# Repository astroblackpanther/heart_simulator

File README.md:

# Heart Simulator Project

## Project Overview
A comprehensive heart simulator project developed during the **International Summer Program Exchange** between **ULACIT (Costa Rica)** and **Rice University (USA)**. This project was completed at the **Oshman Engineering Design Kitchen (OEDK)** as part of the **Rice University George R. Brown School of Engineering and Computing**.

## International Collaboration
- **Home Institution**: ULACIT (Universidad Latinoamericana de Ciencia y Tecnología)
- **Host Institution**: Rice University
- **Program**: International Summer Program Exchange
- **Location**: OEDK (Oshman Engineering Design Kitchen), Rice University
- **Academic Unit**: George R. Brown School of Engineering and Computing

## Project Description
This heart simulator project integrates multiple engineering disciplines including:
- **Biomedical Engineering**: Heart physiology simulation
- **Electrical Engineering**: Circuit design and PCB development
- **Mechanical Engineering**: 3D printed components and mechanical systems
- **Computer Engineering**: Arduino programming and control systems

## Project Structure

### 3D Printing Files
Contains STL files for 3D printed components of the heart simulator, including the main heart model and supporting structures.

### Arduino Code
- **3PIN LCD/ULACIT_2025_3PIN**: Arduino code for 3-pin LCD display configuration
- **4PIN LCD - I2C/ULACIT_2025_4PIN_I2C**: Arduino code for 4-pin I2C LCD display configuration

### KiCad Files
- **Main Schematic ULACIT 2025**: Complete KiCad project files including:
  - `.kicad_prl`: Project file
  - `.kicad_sch`: Schematic design
  - `.kicad_pro`: Project configuration
  - `.kicad_pcb`: PCB layout
  - `.step`: 3D model files
  - `.net`: Netlist files

### PCB Production Board Files
- **GERBER-ULACIT 2025 Button Board**: Manufacturing files for the button control board
- **GERBER-ULACIT 2025 Main Board**: Manufacturing files for the main control board
- Includes `.gbr` (GERBER), `.drl` (drill), and `.pdf` files for PCB production

## Academic Collaboration
This project was developed as part of an international exchange program between ULACIT (Universidad Latinoamericana de Ciencia y Tecnología) and Rice University's George R. Brown School of Engineering and Computing, completed at the Oshman Engineering Design Kitchen (OEDK).

## Future Exploration and Development
Since each participant worked individually on this project, we each possess our own complete set of components including the custom PCBs, 3D printed designs, and fully functional heart simulator. This individual ownership opens up exciting possibilities for continued development and exploration.

### Real-Time Heart Beat Integration
One of the most exciting and viable areas that I am interested in exploring in future development is connecting the LED heart simulation to actual real-time heart beats. I believe that this would create a direct visual representation of your actual heart rhythm, allowing you to see the difference between simulated and real heart beats through the LED patterns. This integration could be achieved through several practical approaches:

#### Wearable Device Integration
- **Smartwatch/Activity Tracker**: Connect to devices like Apple Watch, Fitbit, or Garmin through Bluetooth Low Energy (BLE) to read real-time heart rate data and sync it directly to the LED heart
- **Chest Strap Monitors**: Interface with professional heart rate monitors used in sports and medical applications for high-accuracy heart rate data
- **Smartphone Apps**: Utilize phone-based heart rate monitoring through camera and flash technology, making it accessible to anyone with a smartphone

#### Advanced Features and Applications
- **Real-Time Visualization**: LED patterns that directly mirror actual heart rhythm variations, creating a living, breathing heart display
- **Arrhythmia Detection**: Visual alerts when irregular heartbeats are detected, providing immediate feedback on cardiac health
- **Stress Response Monitoring**: Track how heart rate changes during different activities, exercise, or stress levels
- **Data Logging and Analysis**: Record and analyze heart rate patterns over time for health tracking and research purposes
- **Educational Demonstrations**: Show real-time differences between healthy and stressed heart rhythms for medical education

#### AI/ML Integration and Technical Implementation
- **Machine Learning Algorithms**: Develop predictive models to forecast heart rate patterns and optimize LED animations based on individual physiology
- **Pattern Recognition**: Use AI to identify normal vs. abnormal heart rhythms, stress patterns, and health trends
- **Personalized Health Insights**: Implement AI-driven analysis to provide personalized health recommendations and early warning systems
- **Wireless Communication**: Implement WiFi or Bluetooth modules for seamless data transmission from wearable devices
- **Health Platform Integration**: Connect to health platforms like Apple HealthKit, Google Fit, or Fitbit API for comprehensive health data
- **Cloud Connectivity**: Store and analyze heart rate data for long-term health monitoring and research applications
- **Real-Time Processing**: Optimize the system for immediate response to heart rate changes with minimal latency

### Additional Enhancement Areas
- **AI-Powered Mobile Apps**: Create intelligent companion applications with real-time health analysis and personalized recommendations
- **Machine Learning Research Platform**: Develop the system as a research tool for cardiovascular AI/ML studies and algorithm development
- **Educational Software**: Develop interactive learning modules for medical students with AI-driven case studies and pattern recognition training
- **Research Applications**: Adapt for use in cardiovascular research studies, including AI-based health outcome prediction
- **Commercial Potential**: Explore opportunities for educational or medical device markets with AI-enhanced diagnostic capabilities

### Space Applications and Research
The heart simulator's compact design, low power consumption, and robust construction make it an excellent candidate for space-based applications and research:

#### **Astronaut Health Monitoring**
- **Long-Duration Missions**: Monitor cardiovascular health during extended space travel (Mars missions, lunar bases)
- **Microgravity Effects**: Study how space conditions affect heart rate patterns and cardiovascular adaptation
- **Stress Response**: Track physiological responses to space environment stressors and mission events
- **Preventive Medicine**: Early detection of cardiovascular changes that could affect mission safety

#### **Deep Space Exploration**
- **Mars Mission Readiness**: Test cardiovascular monitoring systems for future Mars missions
- **Autonomous Operation**: Develop self-contained monitoring systems for missions with limited ground support
- **Radiation Effects**: Study how cosmic radiation affects cardiovascular function over extended periods
- **Isolation Studies**: Monitor heart health during long periods of isolation and confinement

#### **Space Research and Development**
- **AI-Enhanced Biomedical Experiments**: Conduct controlled studies on cardiovascular adaptation to space conditions using machine learning for pattern analysis
- **Intelligent Health Monitoring**: Implement AI-driven health prediction systems for long-duration space missions
- **Technology Validation**: Test new AI/ML monitoring technologies in the challenging space environment
- **International Collaboration**: Partner with space agencies worldwide for collaborative AI/ML research in space medicine
- **Educational Outreach**: Inspire future generations through space-based biomedical research with AI integration

This project serves as an excellent foundation for continued innovation in biomedical engineering, combining hardware design, software development, and real-world medical applications.

## Acknowledgments
- **ULACIT**: For the international exchange opportunity
- **Rice University**: For hosting and providing world-class facilities and the knowledge.
- **OEDK Staff**: For guidance and support during the project
---

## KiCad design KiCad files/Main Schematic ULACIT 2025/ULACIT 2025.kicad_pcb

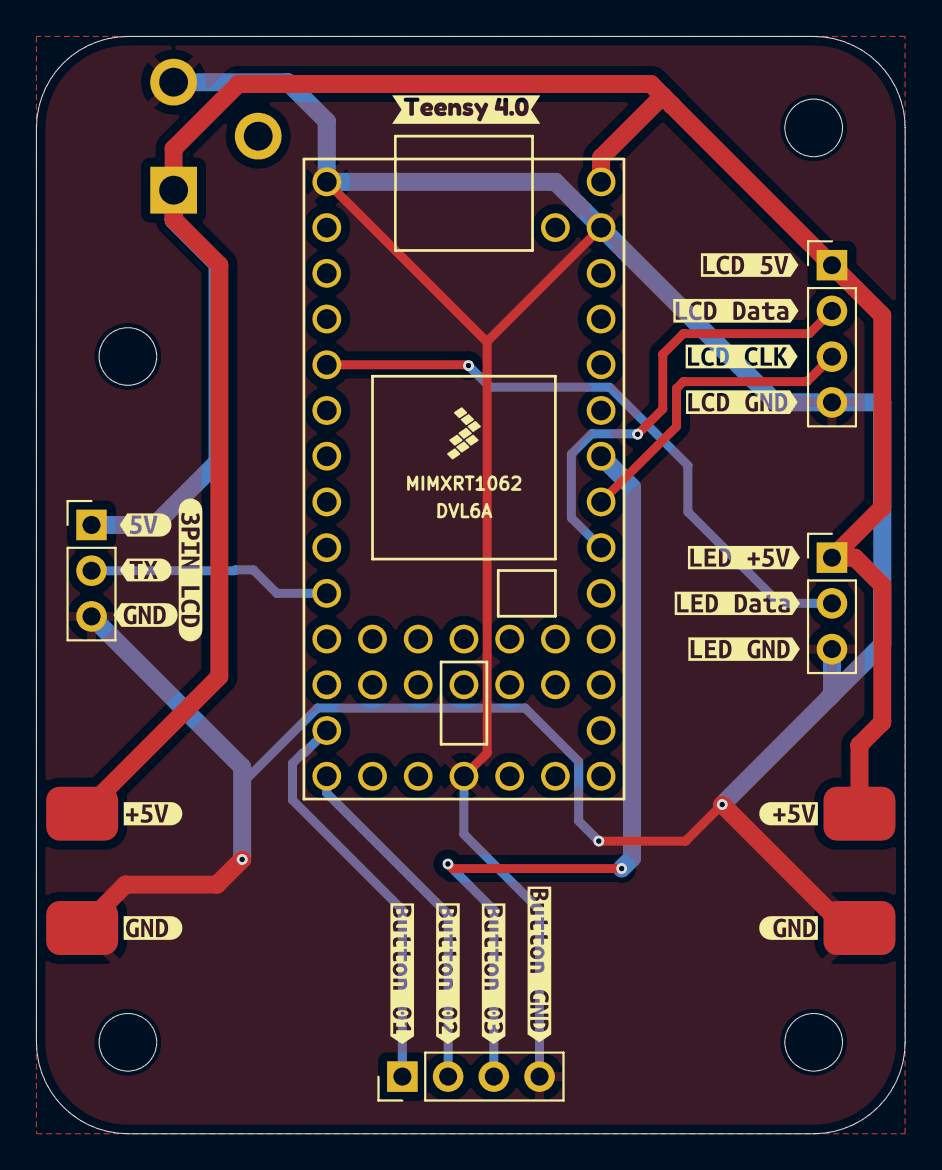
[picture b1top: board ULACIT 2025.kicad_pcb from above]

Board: 2 copper layers, 48.3 x 61.0 mm, 26 parts (1 on the bottom side), 9 nets.

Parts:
J1: Barrel_Jack; BarrelJack_CUI_PJ-102AH_Horizontal
J2: Button Terminal; PinHeader_1x04_P2.54mm_Vertical
J3: LCD Terminal; PinHeader_1x04_P2.54mm_Vertical
J4: LED Terminal; PinHeader_1x03_P2.54mm_Vertical
J6: [OLD] LCD Terminal; PinHeader_1x03_P2.54mm_Vertical
U1: Teensy4.0; Teensy
kibuzzard-6846F3E4: G***; kibuzzard-6846F3E4
kibuzzard-6846F3F3: G***; kibuzzard-6846F3F3
kibuzzard-6846F40C: G***; kibuzzard-6846F40C
kibuzzard-6846F41F: G***; kibuzzard-6846F41F
kibuzzard-68389B9F: G***; kibuzzard-68389B9F
kibuzzard-68389B69: G***; kibuzzard-68389B69
kibuzzard-68389B78: G***; kibuzzard-68389B78
kibuzzard-68389B91: G***; kibuzzard-68389B91
kibuzzard-682631CB: G***; kibuzzard-682631CB
kibuzzard-682631E3: G***; kibuzzard-682631E3
kibuzzard-682631F2: G***; kibuzzard-682631F2
kibuzzard-682633A0: G***; kibuzzard-682633A0
kibuzzard-6826302B: G***; kibuzzard-6826302B
kibuzzard-6826303F: G***; kibuzzard-6826303F
kibuzzard-6838990E: G***; kibuzzard-6838990E
kibuzzard-68263181: G***; kibuzzard-68263181
kibuzzard-68263383: G***; kibuzzard-68263383
kibuzzard-68263394: G***; kibuzzard-68263394
kibuzzard-68263405: G***; kibuzzard-68263405
kibuzzard-68389467: G***; kibuzzard-68389467

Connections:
+5V: J1.1, J3.1, J4.1, J6.1, U1.33 (VIN)
GND: J1.2, J2.4, J3.4, J4.3, J6.3, U1.1 (GND), U1.17 (GND), U1.32 (GND)
unnamed: J2.1, U1.13 (11_MOSI_CTX1)
unnamed: J2.2, U1.14 (12_MISO_MQSL)
unnamed: J2.3, U1.27 (20_A6_TX5_LRCLK1)
unnamed: J3.2, U1.25 (18_A4_SDA0)
unnamed: J3.3, U1.26 (19_A5_SCL0)
unnamed: J4.2, U1.5 (3_LRCLK2)
unnamed: J6.2, U1.10 (8_TX2_IN1)

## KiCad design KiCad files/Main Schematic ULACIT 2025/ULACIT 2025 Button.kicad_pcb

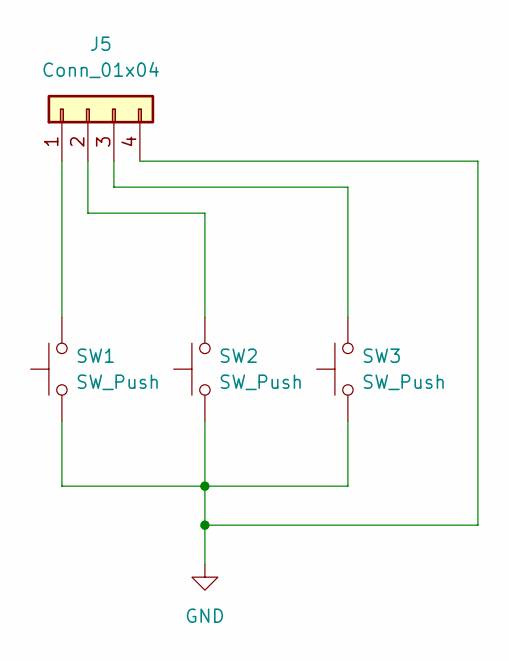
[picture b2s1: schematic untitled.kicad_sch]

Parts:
J5: Conn_01x04; PinHeader_1x04_P2.54mm_Vertical
SW1, SW2, SW3: SW_Push; SW_PUSH_6mm

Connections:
GND: J5.4, SW1.1, SW2.1, SW3.1
unnamed: J5.1, SW1.2
unnamed: J5.2, SW2.2
unnamed: J5.3, SW3.2

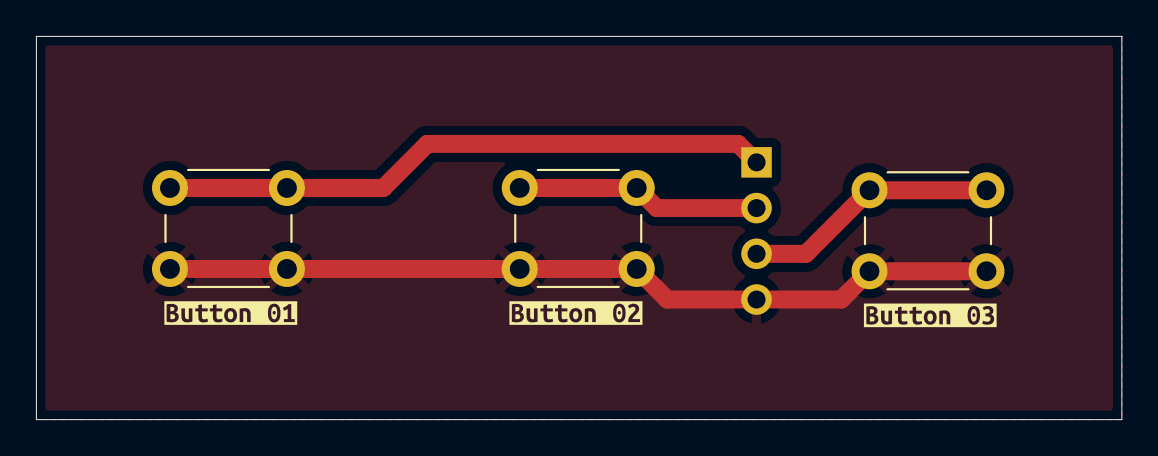
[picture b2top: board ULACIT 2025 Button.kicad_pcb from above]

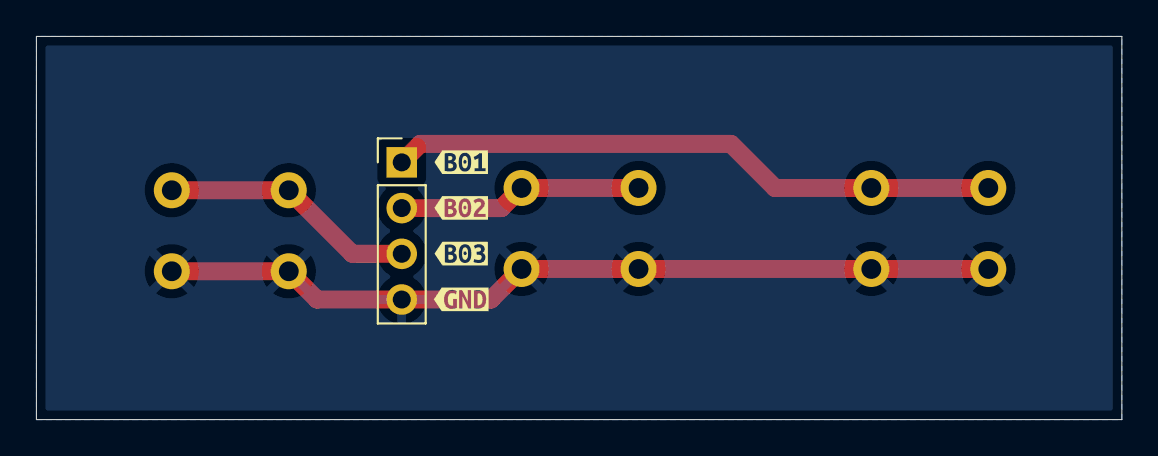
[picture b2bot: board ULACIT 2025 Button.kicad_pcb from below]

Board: 2 copper layers, 60.3 x 21.3 mm, 11 parts (5 on the bottom side), 4 nets.

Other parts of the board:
kibuzzard-6839CA69: G***; kibuzzard-6839CA69
kibuzzard-6839CA74: G***; kibuzzard-6839CA74
kibuzzard-6839CA80: G***; kibuzzard-6839CA80
kibuzzard-6839CAA6: G***; kibuzzard-6839CAA6
kibuzzard-6839CABB: G***; kibuzzard-6839CABB
kibuzzard-6839CAC0: G***; kibuzzard-6839CAC0
kibuzzard-6839CAC5: G***; kibuzzard-6839CAC5

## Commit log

2025-08-24 Initial commit: Add project folder structure and README
2025-08-24 Adding 3D printing STL files for heart simulator components
2025-08-24 Add 3D printing STL files for heart simulator components
2025-08-24 Arduino code files for 3PIN and 4PIN LCD
2025-08-24 Add KiCad project files for main schematic design
2025-08-24 Adding PCB production files for button board and main board
2025-08-24 Update README with comprehensive project details, future exploration, and space applications
2025-08-24 Personalize README with first-person perspective and streamline sections
2025-08-24 Sync README with latest local changes to match GitHub repository
2025-08-24 Refine README tone for professional yet engaging presentation
